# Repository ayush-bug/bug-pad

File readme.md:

# BUGPAD
 This is my first hardware project  bugpad.
 
A 4 keys micropad to play hillclimb racing with and a rotatory encoder and a oled , 

built for hackclub hackpad mission.

# About
This is a  micropad , with 4 switches , 1 encoder and a oled display . 

the switches work as a arrow key , encoder is for volume , and oled show which key is pressed . 

So you can play hillclimb racing and chrome dino with this bug pad .

# Features 
 - four mechanical switches
 - a encoder for volume
 - a oled display
 - and a insane 3d case

# CAD MODEL
 first of all thanks to  <a href="https://stardance.hackclub.com/@Jacube1234">@Jacube1234</a> that help me a lot to learn cad in fusion 360 .

 All cad design is made in fusion 360 

 the case is divided into 3 parts  bottom , top and  plate .

 # PCB
  THE pcd is designed in kicad , also this is my first pcb design , 

  it is quiet is then i thought . 

  i just started and sow some tutorials on yt and done this .
  
Schematic

Layout

Final PCB

# FIRMWARE

my bugpad usage qmk firmware

# BILL OF MATERIAL (BOM)

  - 1  Unsoldered Seeed XIAO RP2040
  - 4x MX-Style switches
  - 1x EC11E Rotary Encoder
  - 4x M3x16mm screws
  - 1x 0.91 inch OLED display
  - custom pcb
  - custom 3d case

# thanks note
 thanks <a href="https://stardance.hackclub.com/@Jacube1234">@Jacube1234</a> and <a href="https://stardance.hackclub.com/@Nemo_Donut">nemo </a>for you help it mean a lot , thanks a lot.

<pre>
  Made with love by Ayush 
</pre>

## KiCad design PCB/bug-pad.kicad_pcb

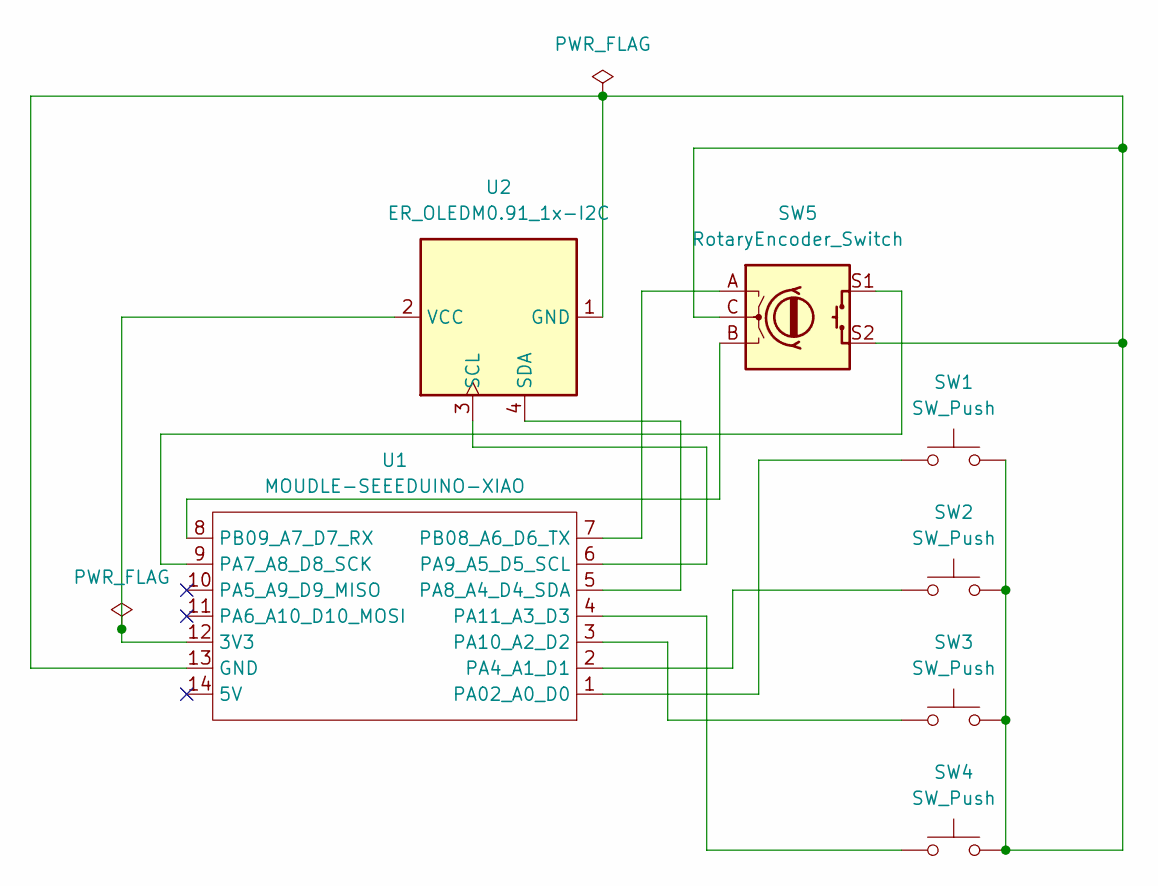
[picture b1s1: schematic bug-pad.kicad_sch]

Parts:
SW1, SW2, SW3, SW4: SW_Push; SW_Cherry_MX_1.00u_PCB
SW5: RotaryEncoder_Switch; RotaryEncoder_Alps_EC11E-Switch_Vertical_H20mm
U1: MOUDLE-SEEEDUINO-XIAO; XIAO-Generic-Hybrid-14P-2.54-21X17.8MM
U2: ER_OLEDM0.91_1x-I2C

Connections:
unnamed: U1.12 (3V3), U2.2 (VCC)
unnamed: SW1.2, SW2.2, SW3.2, SW4.2, SW5.C, SW5.S2, U1.13 (GND), U2.1 (GND)
unnamed: SW1.1, U1.1 (PA02_A0_D0)
unnamed: SW2.1, U1.2 (PA4_A1_D1)
unnamed: SW5.S1, U1.9 (PA7_A8_D8_SCK)
unnamed: U1.5 (PA8_A4_D4_SDA), U2.4 (SDA)
unnamed: U1.6 (PA9_A5_D5_SCL), U2.3 (SCL)
unnamed: SW3.1, U1.3 (PA10_A2_D2)
unnamed: SW4.1, U1.4 (PA11_A3_D3)
unnamed: SW5.A, U1.7 (PB08_A6_D6_TX)
unnamed: SW5.B, U1.8 (PB09_A7_D7_RX)

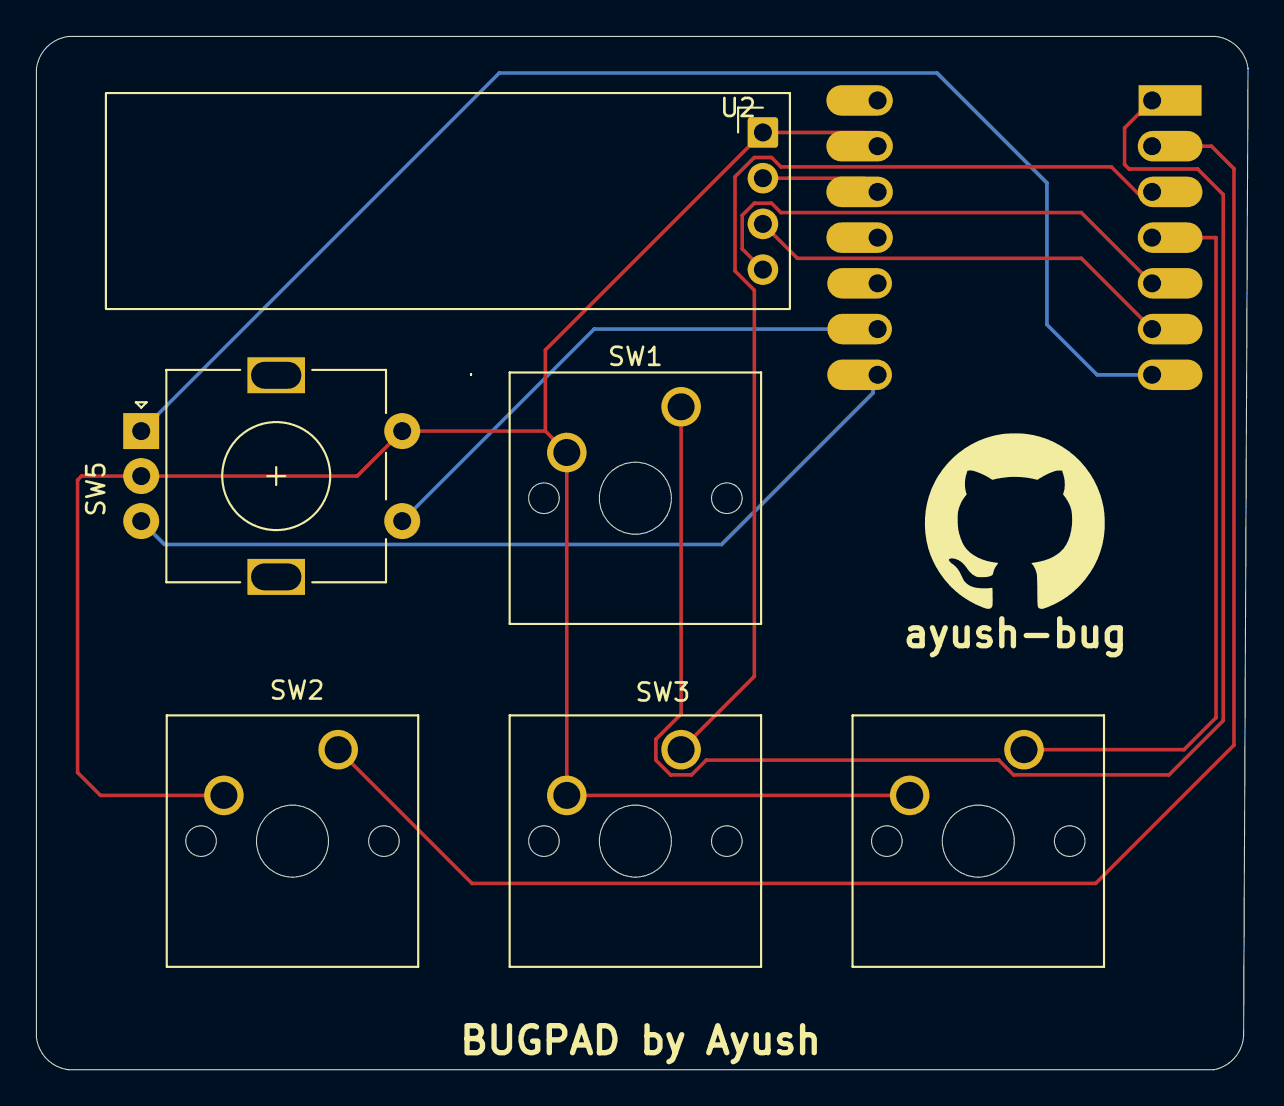
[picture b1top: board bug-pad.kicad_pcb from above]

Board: 2 copper layers, 67.3 x 57.4 mm, 7 parts (1 on the bottom side), 11 nets.

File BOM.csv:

"Reference","Qty","Value","DNP","Exclude from BOM","Exclude from Board","Exclude from Simulation","Exclude from Position Files","Footprint","Datasheet"
"SW1,SW2,SW3,SW4","4","SW_Push","","","","","${EXCLUDE_FROM_POS_FILES}","Button_Switch_Keyboard:SW_Cherry_MX_1.00u_PCB",""
"SW5","1","RotaryEncoder_Switch","","","","","${EXCLUDE_FROM_POS_FILES}","Rotary_Encoder:RotaryEncoder_Alps_EC11E-Switch_Vertical_H20mm",""
"U1","1","MOUDLE-SEEEDUINO-XIAO","","","","","${EXCLUDE_FROM_POS_FILES}","footprints:XIAO-Generic-Hybrid-14P-2.54-21X17.8MM",""
"U2","1","ER_OLEDM0.91_1x-I2C","","","","","${EXCLUDE_FROM_POS_FILES}","Display:ER_OLEDM0.91_1x-I2C","https://www.buydisplay.com/download/manual/ER-OLEDM0.91-1_Da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"
